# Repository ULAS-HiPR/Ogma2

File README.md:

# Ogma 2

HiPR's workhorse flight computer: **Burrito** (Croí2), the flight board, and
**Churro** (Foinse2), an MCU-less power board. **Fajita** is the separate
propulsion controller. The capture specification is ready; capture waits for
Seán's go-ahead after the 3 November review, and native CAD holds the
8 September draft. Nothing is built or flown yet.

**Start here:** [system tour](docs/architecture/system-tour.md) →
[decisions](decisions.md) → the chapter for your block.

## Read in this order

1. [System tour](docs/architecture/system-tour.md): boards, power, data, connectors with photos.
2. [Decisions](decisions.md): what is settled, what is proposed, what is open.
3. [Current system](current-system.md): what is true now.
4. [Requirements](docs/requirements/README.md): Burrito's, frozen 21 Nov; Churro's, draft. Then the [behaviour map](docs/architecture/behaviour-map.md).
5. [Block chapters](docs/architecture/README.md): one page per block, plus the capture specification.
6. [Hardware](hardware/README.md) for CAD, or the [firmware interface](docs/firmware-interface.md) for firmware.
7. [Verification](docs/architecture/11-verification.md): release gates and what has to pass.

Don't start at the project log or `docs/archive/`.

## Repository

| Path | Contents |
| --- | --- |
| `hardware/croi2/`, `hardware/foinse2/` | Native KiCad projects, tracked directly; no submodules |
| `docs/requirements/` | Requirements with their sources, mechanisms and verification; the dated rules sweep |
| `docs/architecture/` | Block chapters, behaviour map, capture specification, justifications |
| `interfaces/` | Owned contracts: power, flight fault, reset, vehicle boundary |
| `docs/archive/` | Superseded reviews, studies and history: evidence, not instructions |
| `project-log.md` | Append-only history |

Use branches and bounded pull requests. `main` is reviewed truth once merged.
Native CAD, contracts and measurements outrank prose. No raw transcripts,
private correspondence, generated dumps or render trees. No licence selected;
Rev 1 is a separate project.

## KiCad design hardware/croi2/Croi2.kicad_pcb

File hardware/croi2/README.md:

# Croi2

21 November 2026. Schematic captured from the [capture specification](../../docs/architecture/schematic-capture-spec.md)
(D-21Nov.9). Engineering draft: not ready for manufacture or flight.

Open [Croi2.kicad_pro](Croi2.kicad_pro), then its schematic and PCB from that project.
Reopen old editors without saving stale in-memory drawings over these files.

44 schematic pages, 570 physical symbols. Each circuit explains what it does and
what it connects to. Follow the root index, then trace the local wires. Labels
identify connections between sheets. The capture steps, their checks and what is
still owed are in [schematic-status.md](schematic-status.md).

The PCB has not been updated from this schematic yet: it still holds the
8 September parts and placements, so schematic/PCB parity is broken until layout.
[board-checks.json](board-checks.json), [native-identity-checks.json](native-identity-checks.json)
and [placement-report.json](placement-report.json) describe that older PCB.

- [Current engineering status](schematic-status.md).
- [Schematic checks](full-checks.json): netlist parity, the as-captured pin maps
  ([flight](libraries/inputs/flight-pinout.csv), [comms](libraries/inputs/comms-pinout.csv))
  and the capture safety assertions, from [tools/check_schematic_full.py](tools/check_schematic_full.py).
- [Local library inventory](libraries/board-library-manifest.json).
- [JLC stock](jlc-stock.md).
- [Architecture reading pack](../../docs/architecture/README.md).
- [8 September exports and pin maps](history/baseline-2026-09-08/), and the
  [earlier README](history/pre-readable-2026-09-08/README.md), preserved as history.

ERC: no finding, with three recorded exclusions (strap pins tied to GND; reasons in
the project file). J101 still has no footprint (Molex Nano-Fit drawing not yet
obtained) and J6101 / J6102 are placeholders until their parts are chosen. Energy
links R6310 / R6410 / R6510 stay DNP. Do not connect initiators.

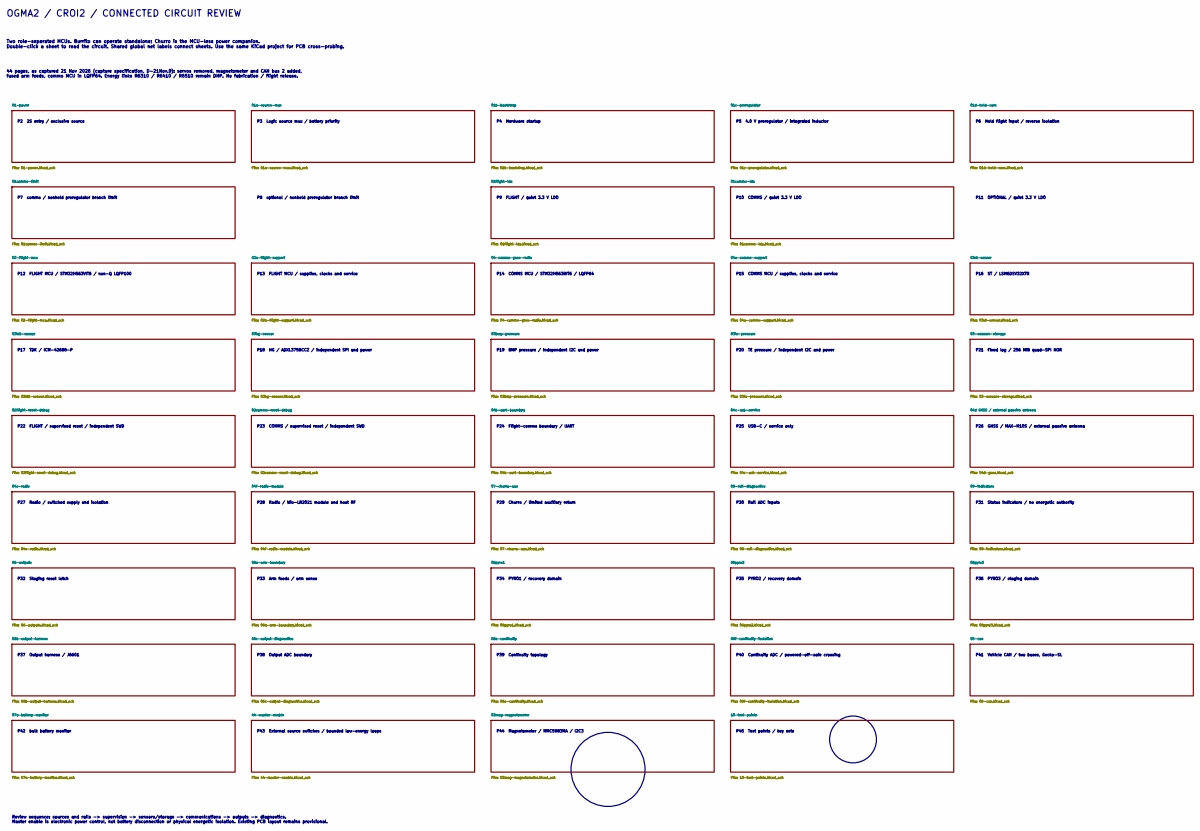
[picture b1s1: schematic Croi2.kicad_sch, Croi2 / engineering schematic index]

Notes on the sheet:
P7 comms / nonheld preregulator branch limit
P30 Rail ADC inputs
P5 4.0 V preregulator / integrated inductor
44 pages, as captured 21 Nov 2026 (capture specification, D-21Nov.9): servos removed, magnetometer and CAN bus 2 added, fused arm feeds, comms MCU in LQFP64. Energy links R6310 / R6410 / R6510 remain DNP. No fabrication / flight release.
P27 Radio / switched supply and isolation
P10 COMMS / quiet 3.3 V LDO
P31 Status indicators / no energetic authority
P8 optional / nonheld preregulator branch limit
P26 GNSS / MAX-M10S / external passive antenna
P18 HG / ADXL375BCCZ / independent SPI and power
P39 Continuity topology
P44 Magnetometer / MMC5983MA / I2C3
P45 Test points / key nets
P21 Fixed log / 256 MiB quad-SPI NOR
P32 Staging reset latch
P43 External source switches / bounded low-energy loops
P34 PYRO1 / recovery domain
P28 Radio / Wio-LR2021 module and host RF
P41 Vehicle CAN / two buses, Gecko-SL
P42 bulk battery monitor
P20 TE pressure / independent I2C and power
OGMA2 / CROI2 / CONNECTED CIRCUIT REVIEW
P14 COMMS MCU / STM32H563RIT6 / LQFP64
P15 COMMS MCU / supplies, clocks and service
P13 FLIGHT MCU / supplies, clocks and service
P9 FLIGHT / quiet 3.3 V LDO
P3 Logic source mux / battery priority
P19 BMP pressure / independent I2C and power
P35 PYRO2 / recovery domain
P4 Hardware startup
P11 OPTIONAL / quiet 3.3 V LDO
P25 USB-C / service only
P6 Held flight input / reverse isolation
P2 2S entry / exclusive source
P40 Continuity ADC / powered-off-safe crossing
P22 FLIGHT / supervised reset / independent SWD
P24 Flight-comms boundary / UART
P17 TDK / ICM-42688-P
P23 COMMS / supervised reset / independent SWD
P16 ST / LSM6DSV32XTR

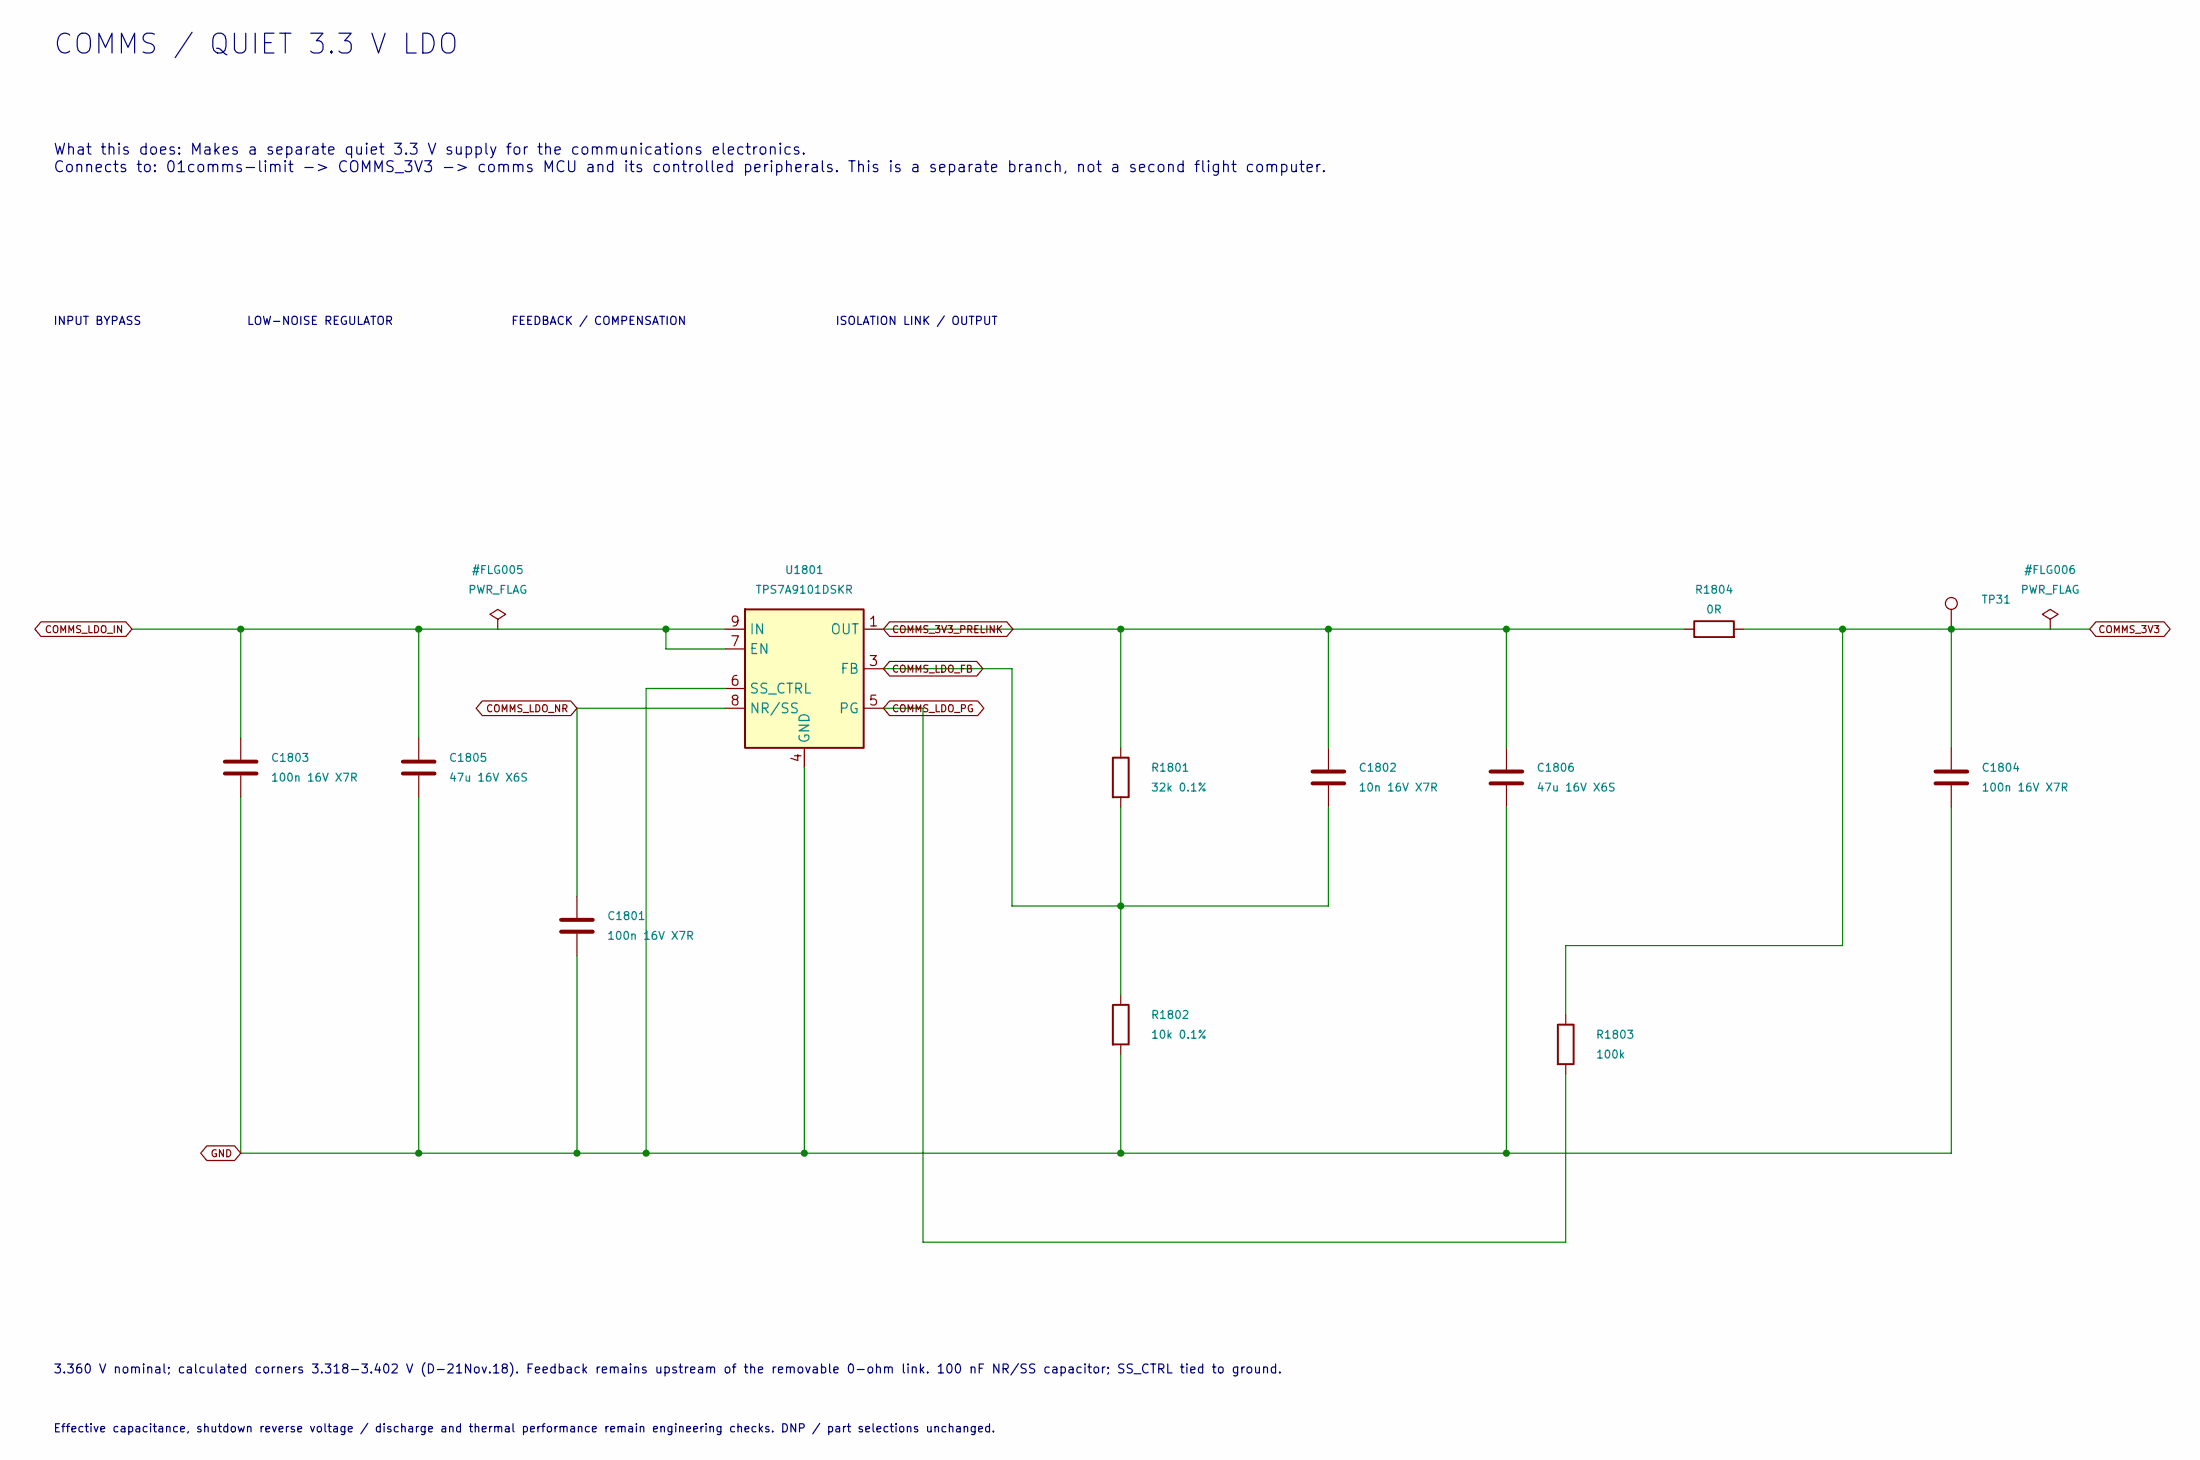
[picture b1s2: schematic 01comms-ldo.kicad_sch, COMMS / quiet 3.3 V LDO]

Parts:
C1801, C1803, C1804: 100n 16V X7R; C_0402_1005Metric; MPN CL05B104KB54PNC; LCSC C307331
C1802: 10n 16V X7R; C_0402_1005Metric; MPN CL05B103KB5NNNC; LCSC C15195
C1805, C1806: 47u 16V X6S; C_1210_3225Metric; MPN GRM32EC81C476KE15L
R1801: 32k 0.1%; R_0603_1608Metric
R1802: 10k 0.1%; R_0603_1608Metric
R1803: 100k; R_0402_1005Metric; MPN 0402WGF1003TCE; LCSC C25741
R1804: 0R; R_0603_1608Metric
TP31: COMMS_3V3; TestPoint_Keystone_5190TR_ColorKeyed; MPN 5194TR; LCSC C22388408
U1801: TPS7A9101DSKR; MPN TPS7A9101DSKR

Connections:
COMMS_3V3: C1804.1, R1803.1, R1804.2, TP31.1 (1_1); also elsewhere on the board
COMMS_3V3_PRELINK: C1802.1, C1806.1, R1801.1, R1804.1, U1801.1 (OUT), U1801.2 (OUT)
COMMS_LDO_FB: C1802.2, R1801.2, R1802.1, U1801.3 (FB)
COMMS_LDO_IN: C1803.1, C1805.1, U1801.7 (EN), U1801.9 (IN), U1801.10 (IN); also elsewhere on the board
COMMS_LDO_NR: C1801.1, U1801.8 (NR/SS)
COMMS_LDO_PG: R1803.2, U1801.5 (PG); also elsewhere on the board
GND: C1801.2, C1803.2, C1804.2, C1805.2, C1806.2, R1802.2, U1801.4 (GND), U1801.6 (SS_CTRL), U1801.11 (GND); also elsewhere on the board

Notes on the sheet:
COMMS / QUIET 3.3 V LDO
What this does: Makes a separate quiet 3.3 V supply for the communications electronics. Connects to: 01comms-limit -> COMMS_3V3 -> comms MCU and its controlled peripherals. This is a separate branch, not a second flight computer.
Effective capacitance, shutdown reverse voltage / discharge and thermal performance remain engineering checks. DNP / part selections unchanged.
INPUT BYPASS LOW-NOISE REGULATOR FEEDBACK / COMPENSATION ISOLATION LINK / OUTPUT
3.360 V nominal; calculated corners 3.318-3.402 V (D-21Nov.18). Feedback remains upstream of the removable 0-ohm link. 100 nF NR/SS capacitor; SS_CTRL tied to ground.

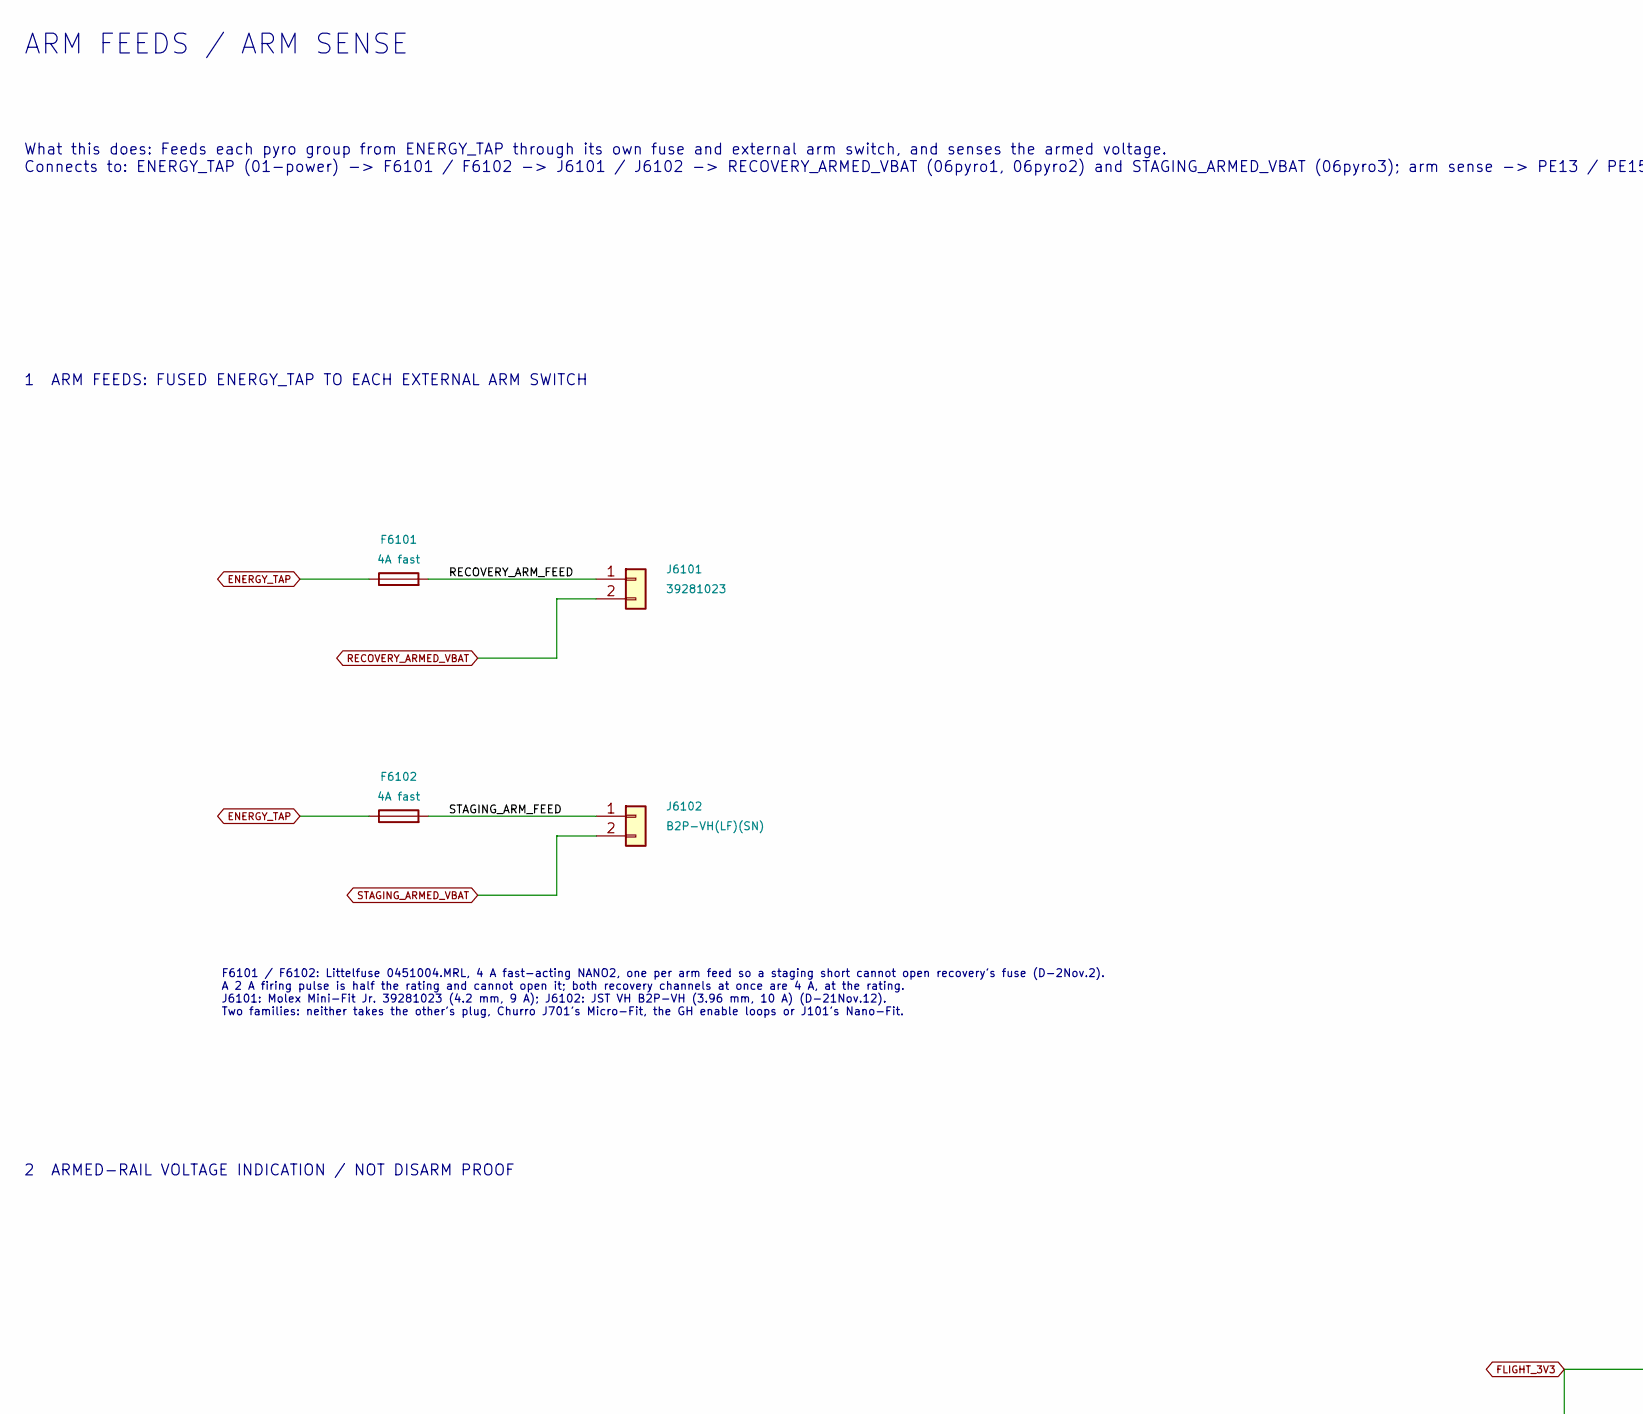
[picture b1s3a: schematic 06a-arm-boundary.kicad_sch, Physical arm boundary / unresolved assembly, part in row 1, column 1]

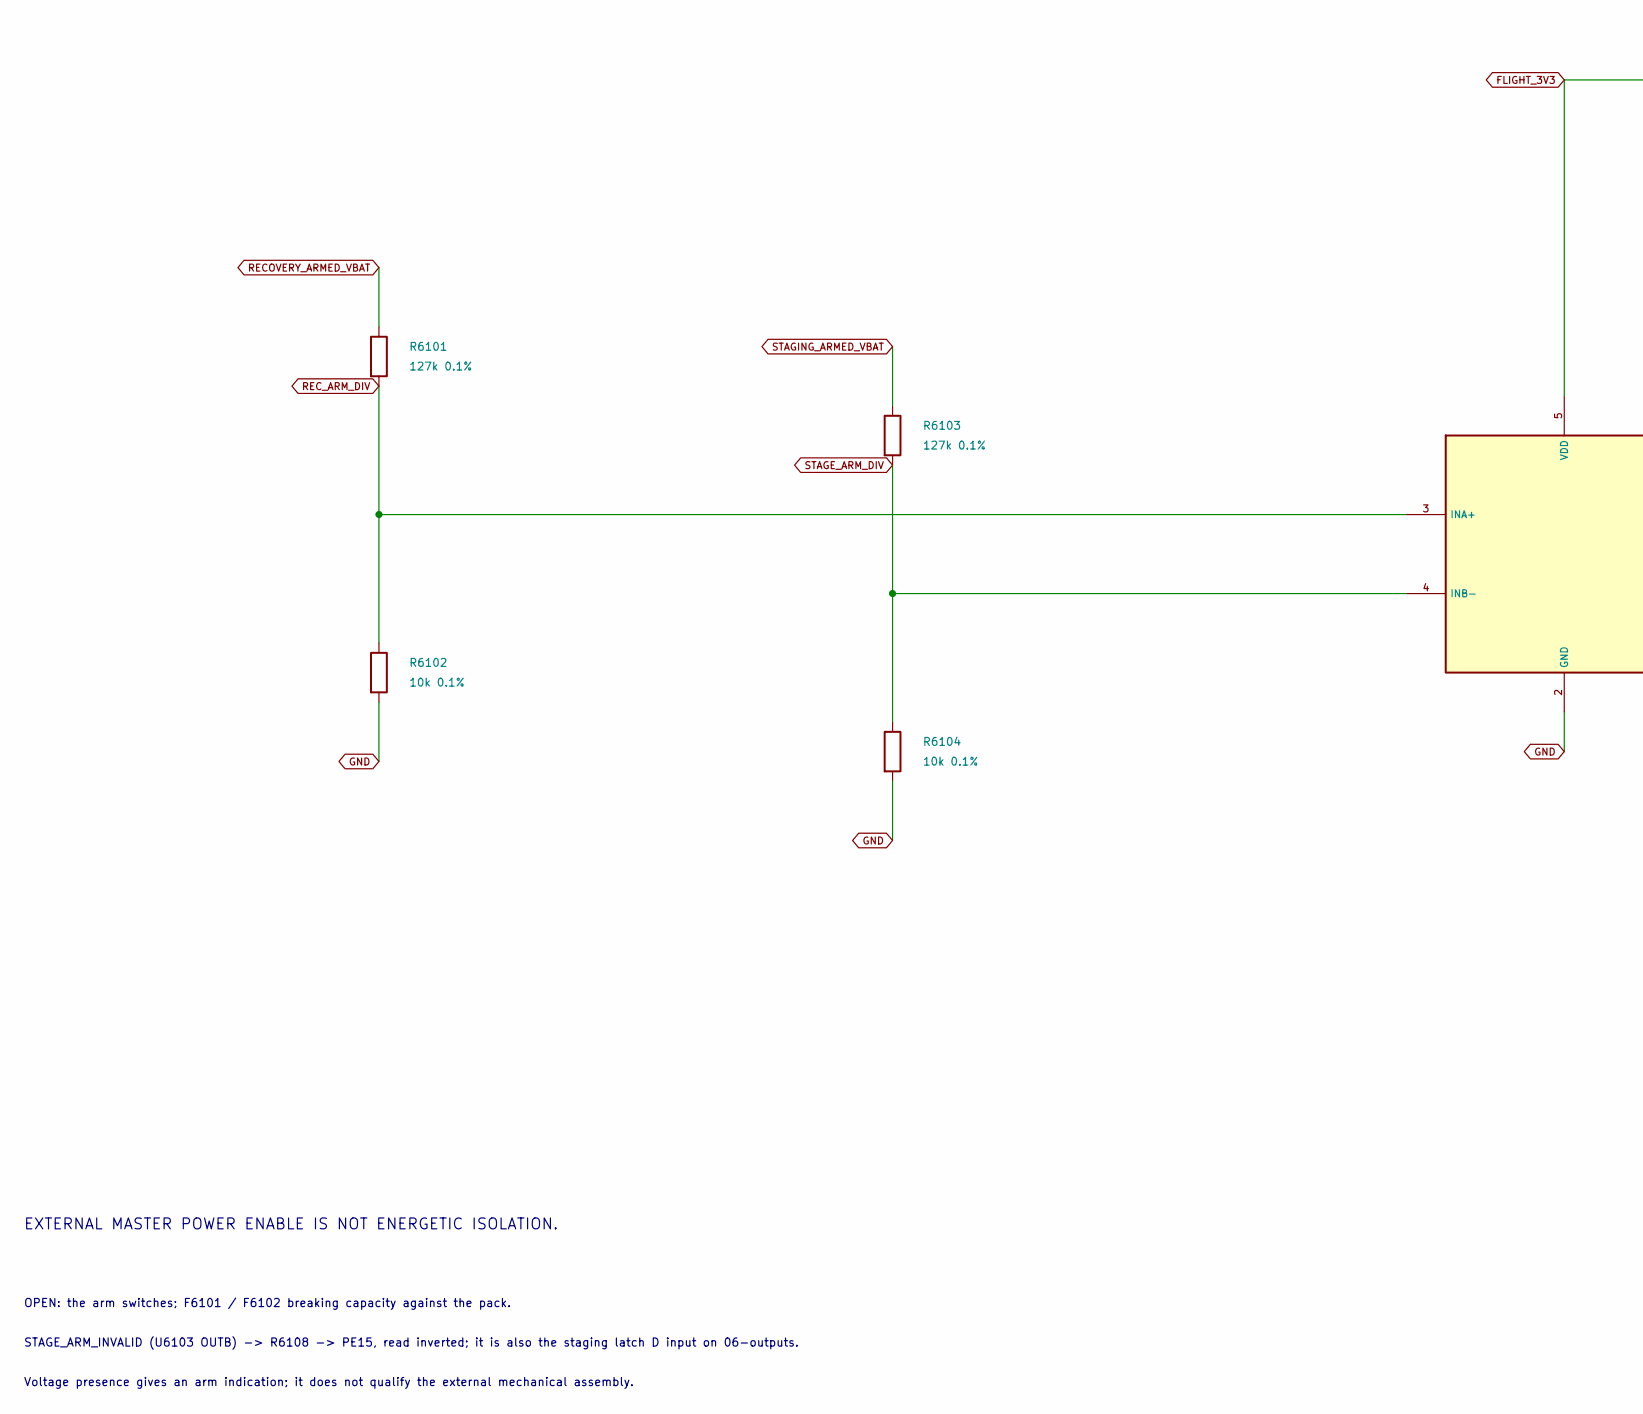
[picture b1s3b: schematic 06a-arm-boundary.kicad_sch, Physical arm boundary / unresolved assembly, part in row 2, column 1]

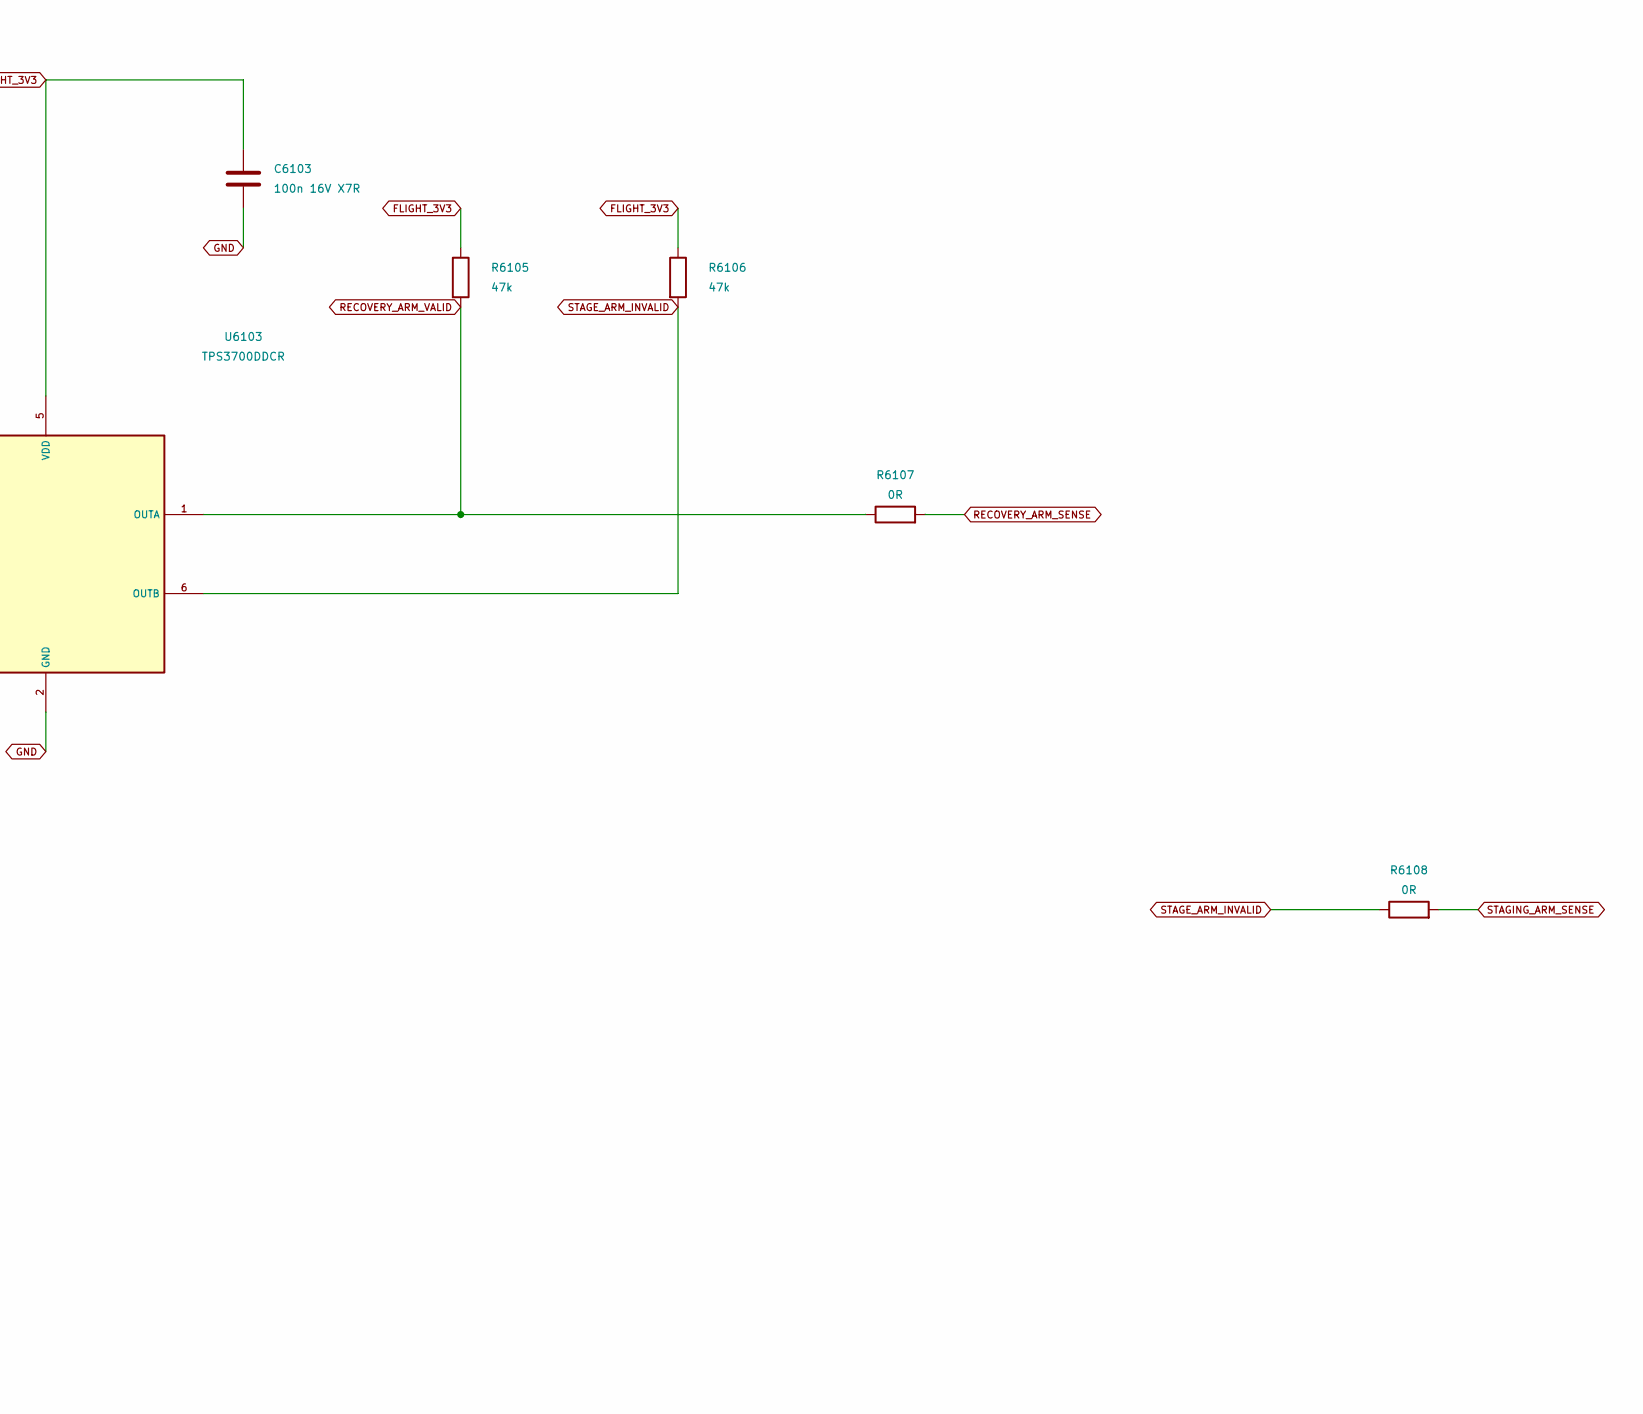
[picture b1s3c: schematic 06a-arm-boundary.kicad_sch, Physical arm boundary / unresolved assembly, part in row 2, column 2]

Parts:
C6103: 100n 16V X7R; C_0603_1608Metric
F6101, F6102: 4A fast; Fuse_Littelfuse-NANO2-451_453; MPN 0451004.MRL
J6101: 39281023; Molex_Mini-Fit_Jr_5566-02A_2x01_P4.20mm_Vertical; MPN 39281023
J6102: B2P-VH(LF)(SN); JST_VH_B2P-VH_1x02_P3.96mm_Vertical; MPN B2P-VH(LF)(SN)
R6101, R6103: 127k 0.1%; R_0603_1608Metric
R6102, R6104: 10k 0.1%; R_0603_1608Metric
R6105, R6106: 47k; R_0603_1608Metric
R6107, R6108: 0R; R_0603_1608Metric
U6103: TPS3700DDCR; MPN TPS3700DDCR

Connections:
/06a-arm-boundary/RECOVERY_ARM_FEED: F6101.2, J6101.1
/06a-arm-boundary/STAGING_ARM_FEED: F6102.2, J6102.1
ENERGY_TAP: F6101.1, F6102.1; also elsewhere on the board
FLIGHT_3V3: C6103.1, R6105.1, R6106.1, U6103.5 (VDD); also elsewhere on the board
GND: C6103.2, R6102.2, R6104.2, U6103.2 (GND); also elsewhere on the board
RECOVERY_ARMED_VBAT: J6101.2, R6101.1; also elsewhere on the board
RECOVERY_ARM_SENSE: R6107.2; also elsewhere on the board
RECOVERY_ARM_VALID: R6105.2, R6107.1, U6103.1 (OUTA)
REC_ARM_DIV: R6101.2, R6102.1, U6103.3 (INA+)
STAGE_ARM_DIV: R6103.2, R6104.1, U6103.4 (INB-)
STAGE_ARM_INVALID: R6106.2, R6108.1, U6103.6 (OUTB); also elsewhere on the board
STAGING_ARMED_VBAT: J6102.2, R6103.1; also elsewhere on the board
STAGING_ARM_SENSE: R6108.2; also elsewhere on the board

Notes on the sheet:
OPEN: the arm switches; F6101 / F6102 breaking capacity against the pack.
What this does: Feeds each pyro group from ENERGY_TAP through its own fuse and external arm switch, and senses the armed voltage. Connects to: ENERGY_TAP (01-power) -> F6101 / F6102 -> J6101 / J6102 -> RECOVERY_ARMED_VBAT (06pyro1, 06pyro2) and STAGING_ARMED_VBAT (06pyro3); arm sense -> PE13 / PE15.
ARM FEEDS / ARM SENSE
EXTERNAL MASTER POWER ENABLE IS NOT ENERGETIC ISOLATION.
F6101 / F6102: Littelfuse 0451004.MRL, 4 A fast-acting NANO2, one per arm feed so a staging short cannot open recovery's fuse (D-2Nov.2). A 2 A firing pulse is half the rating and cannot open it; both recovery channels at once are 4 A, at the rating. J6101: Molex Mini-Fit Jr. 39281023 (4.2 mm, 9 A)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
2 ARMED-RAIL VOLTAGE INDICATION / NOT DISARM PROOF
STAGE_ARM_INVALID (U6103 OUTB) -> R6108 -> PE15, read inverted; it is also the staging latch D input on 06-outputs.
1 ARM FEEDS: FUSED ENERGY_TAP TO EACH EXTERNAL ARM SWITCH
Voltage presence gives an arm indication; it does not qualify the external mechanical assembly.

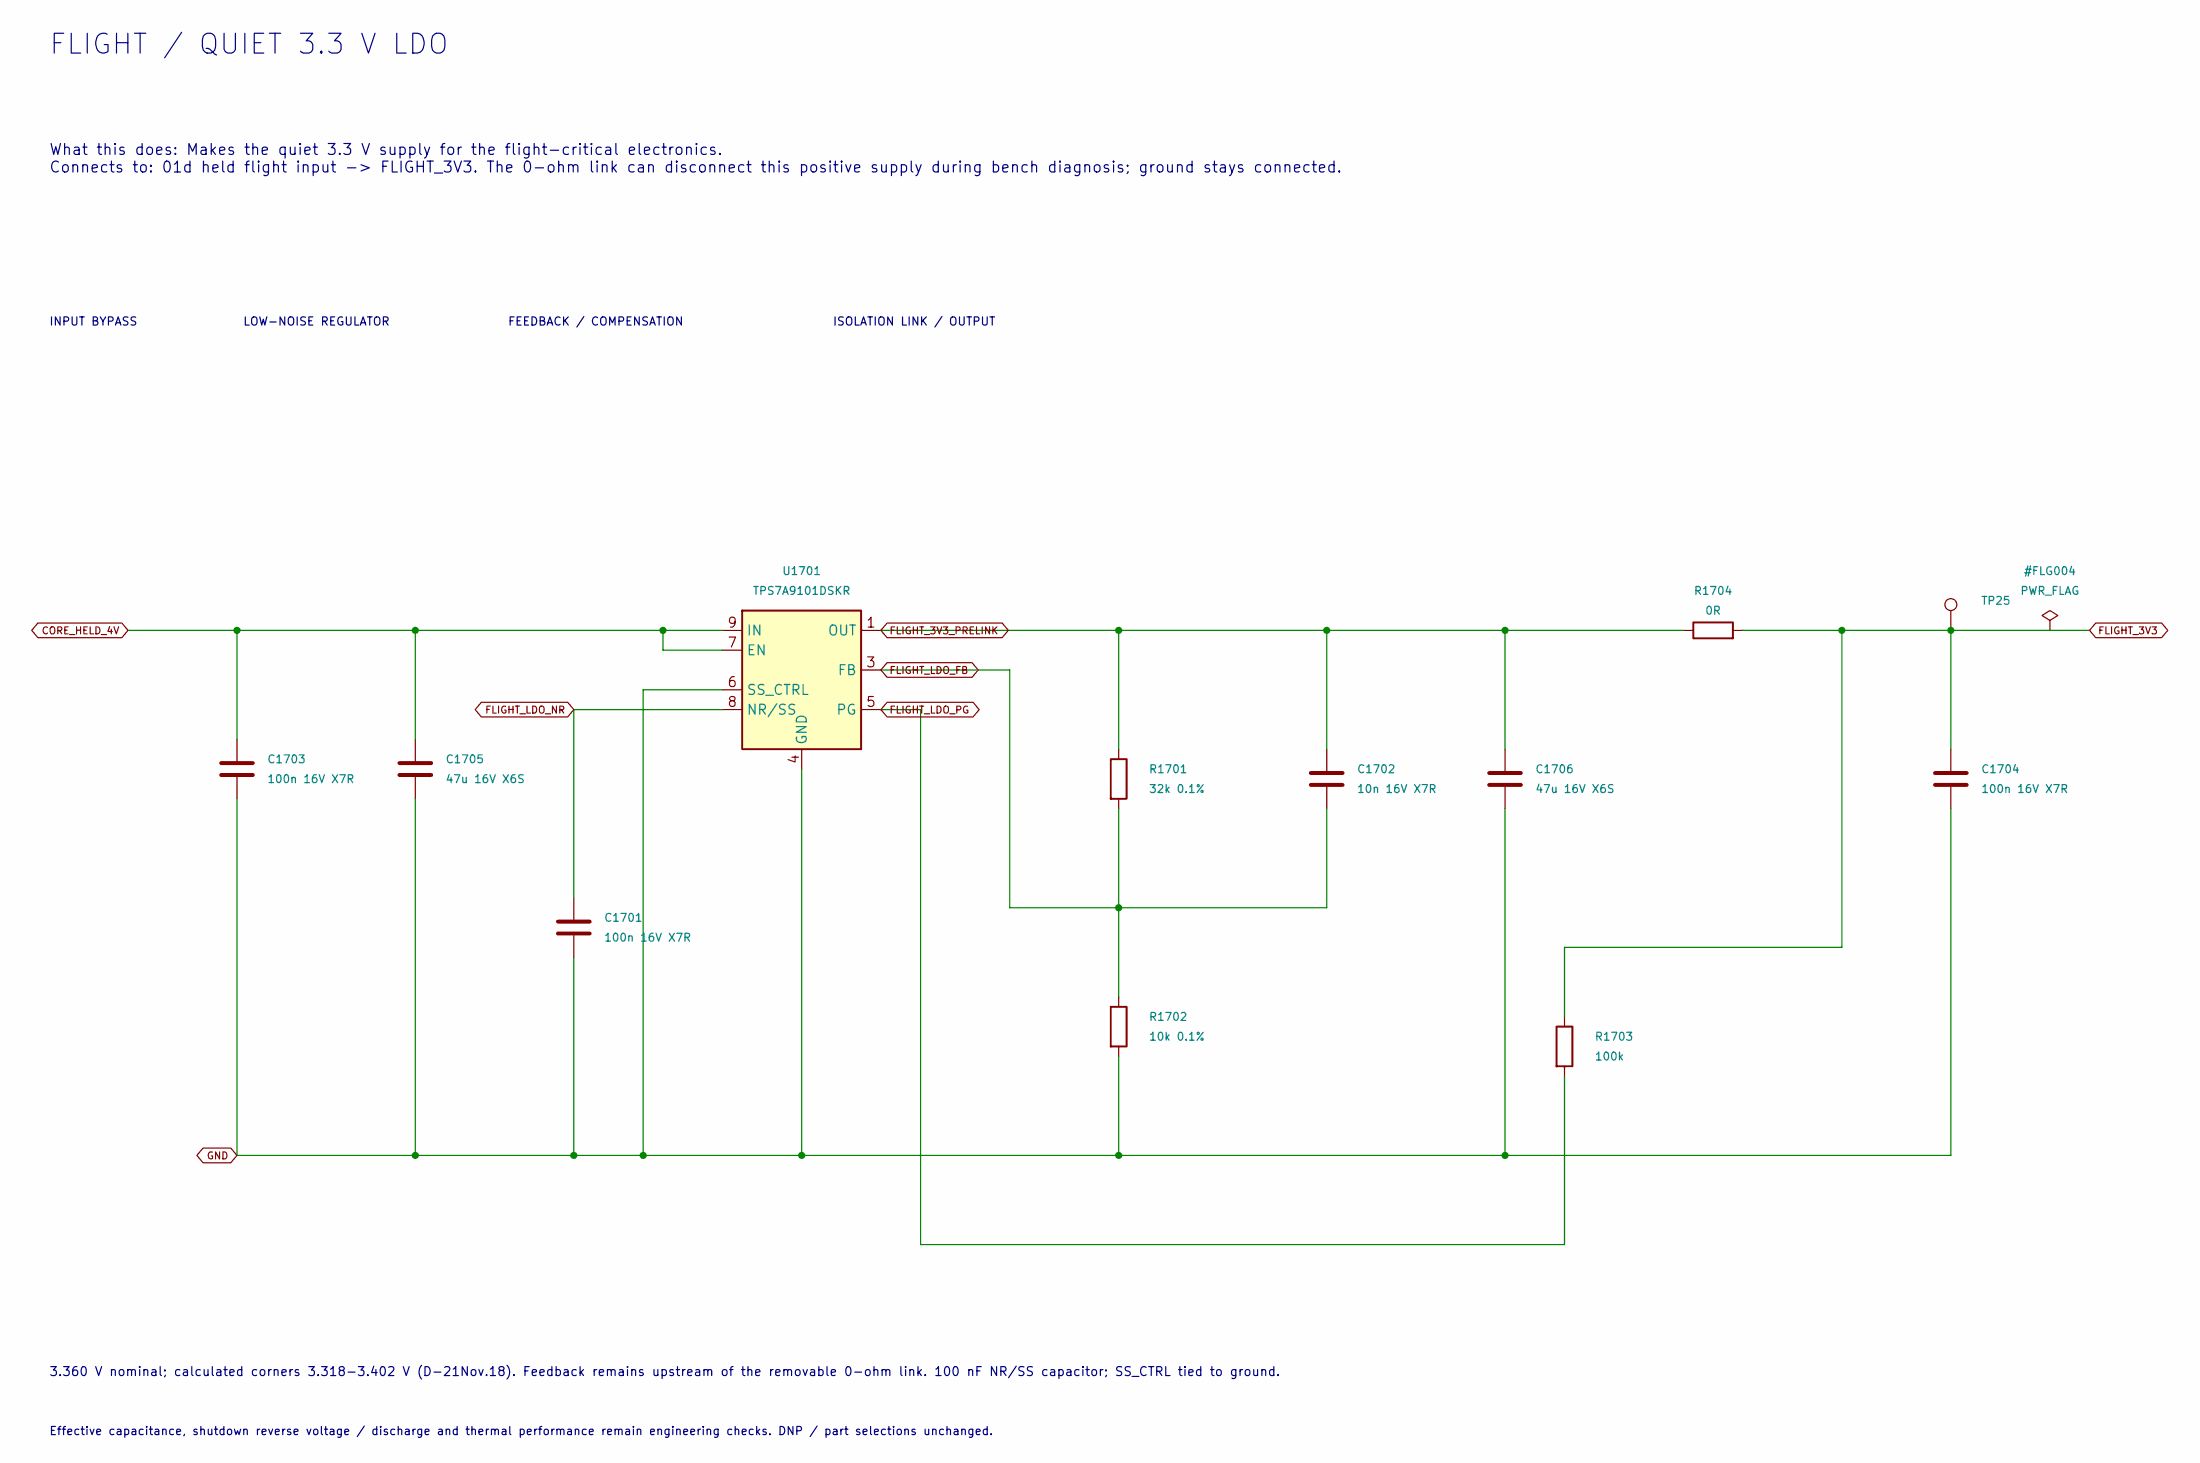
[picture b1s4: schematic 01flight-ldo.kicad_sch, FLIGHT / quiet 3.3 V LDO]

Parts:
C1701, C1703, C1704: 100n 16V X7R; C_0402_1005Metric; MPN CL05B104KB54PNC; LCSC C307331
C1702: 10n 16V X7R; C_0402_1005Metric; MPN CL05B103KB5NNNC; LCSC C15195
C1705, C1706: 47u 16V X6S; C_1210_3225Metric; MPN GRM32EC81C476KE15L
R1701: 32k 0.1%; R_0603_1608Metric
R1702: 10k 0.1%; R_0603_1608Metric
R1703: 100k; R_0402_1005Metric; MPN 0402WGF1003TCE; LCSC C25741
R1704: 0R; R_0603_1608Metric
TP25: FLIGHT_3V3; TestPoint_Keystone_5190TR_ColorKeyed; MPN 5194TR; LCSC C22388408
U1701: TPS7A9101DSKR; MPN TPS7A9101DSKR

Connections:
CORE_HELD_4V: C1703.1, C1705.1, U1701.7 (EN), U1701.9 (IN), U1701.10 (IN); also elsewhere on the board
FLIGHT_3V3: C1704.1, R1703.1, R1704.2, TP25.1 (1_1); also elsewhere on the board
FLIGHT_3V3_PRELINK: C1702.1, C1706.1, R1701.1, R1704.1, U1701.1 (OUT), U1701.2 (OUT)
FLIGHT_LDO_FB: C1702.2, R1701.2, R1702.1, U1701.3 (FB)
FLIGHT_LDO_NR: C1701.1, U1701.8 (NR/SS)
FLIGHT_LDO_PG: R1703.2, U1701.5 (PG); also elsewhere on the board
GND: C1701.2, C1703.2, C1704.2, C1705.2, C1706.2, R1702.2, U1701.4 (GND), U1701.6 (SS_CTRL), U1701.11 (GND); also elsewhere on the board

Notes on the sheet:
FLIGHT / QUIET 3.3 V LDO
What this does: Makes the quiet 3.3 V supply for the flight-critical electronics. Connects to: 01d held flight input -> FLIGHT_3V3. The 0-ohm link can disconnect this positive supply during bench diagnosis; ground stays connected.
3.360 V nominal; calculated corners 3.318-3.402 V (D-21Nov.18). Feedback remains upstream of the removable 0-ohm link. 100 nF NR/SS capacitor; SS_CTRL tied to ground.
INPUT BYPASS LOW-NOISE REGULATOR FEEDBACK / COMPENSATION ISOLATION LINK / OUTPUT
Effective capacitance, shutdown reverse voltage / discharge and thermal performance remain engineering checks. DNP / part selections unchanged.
